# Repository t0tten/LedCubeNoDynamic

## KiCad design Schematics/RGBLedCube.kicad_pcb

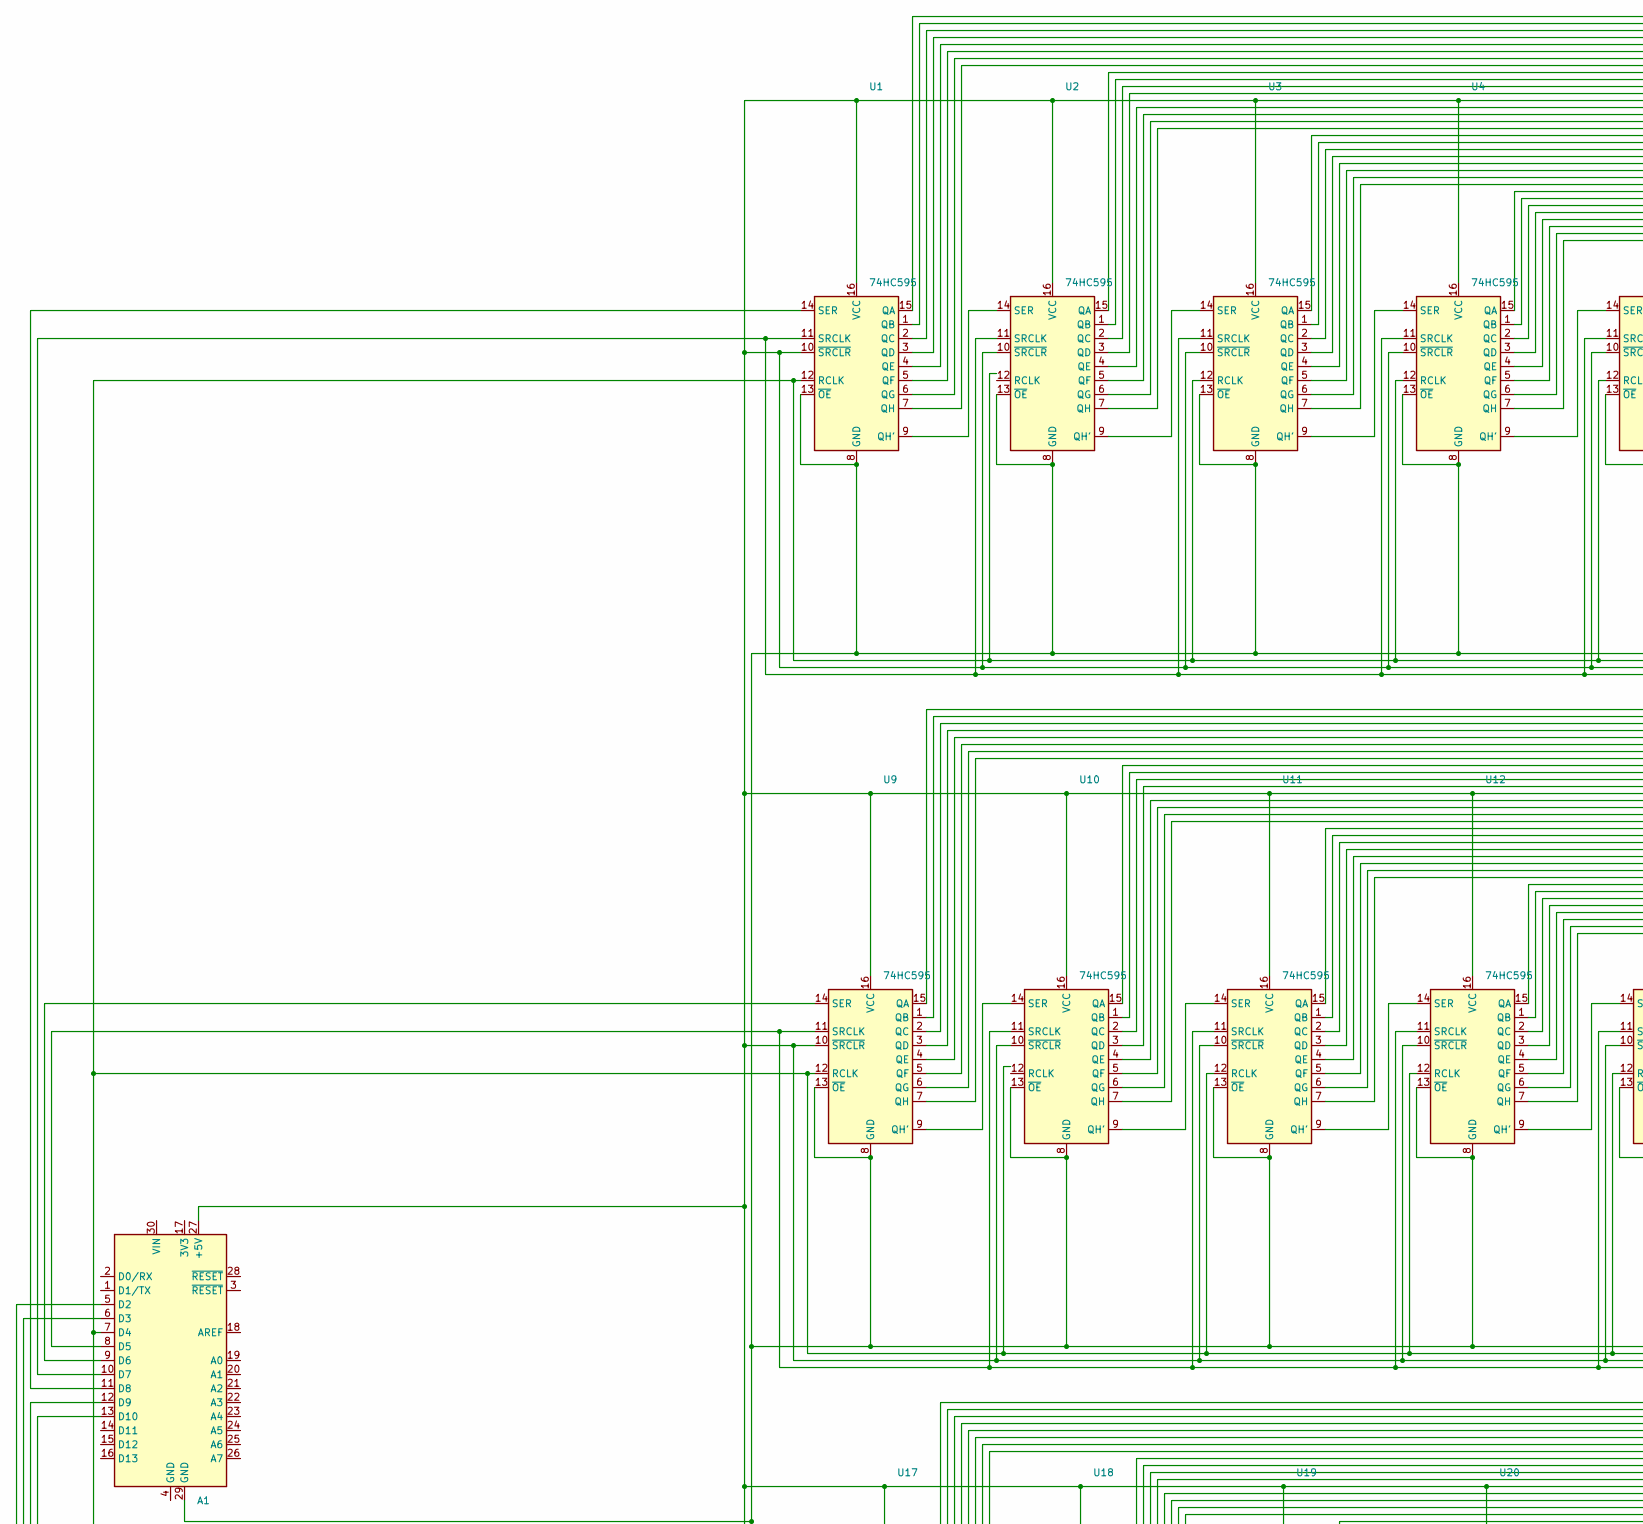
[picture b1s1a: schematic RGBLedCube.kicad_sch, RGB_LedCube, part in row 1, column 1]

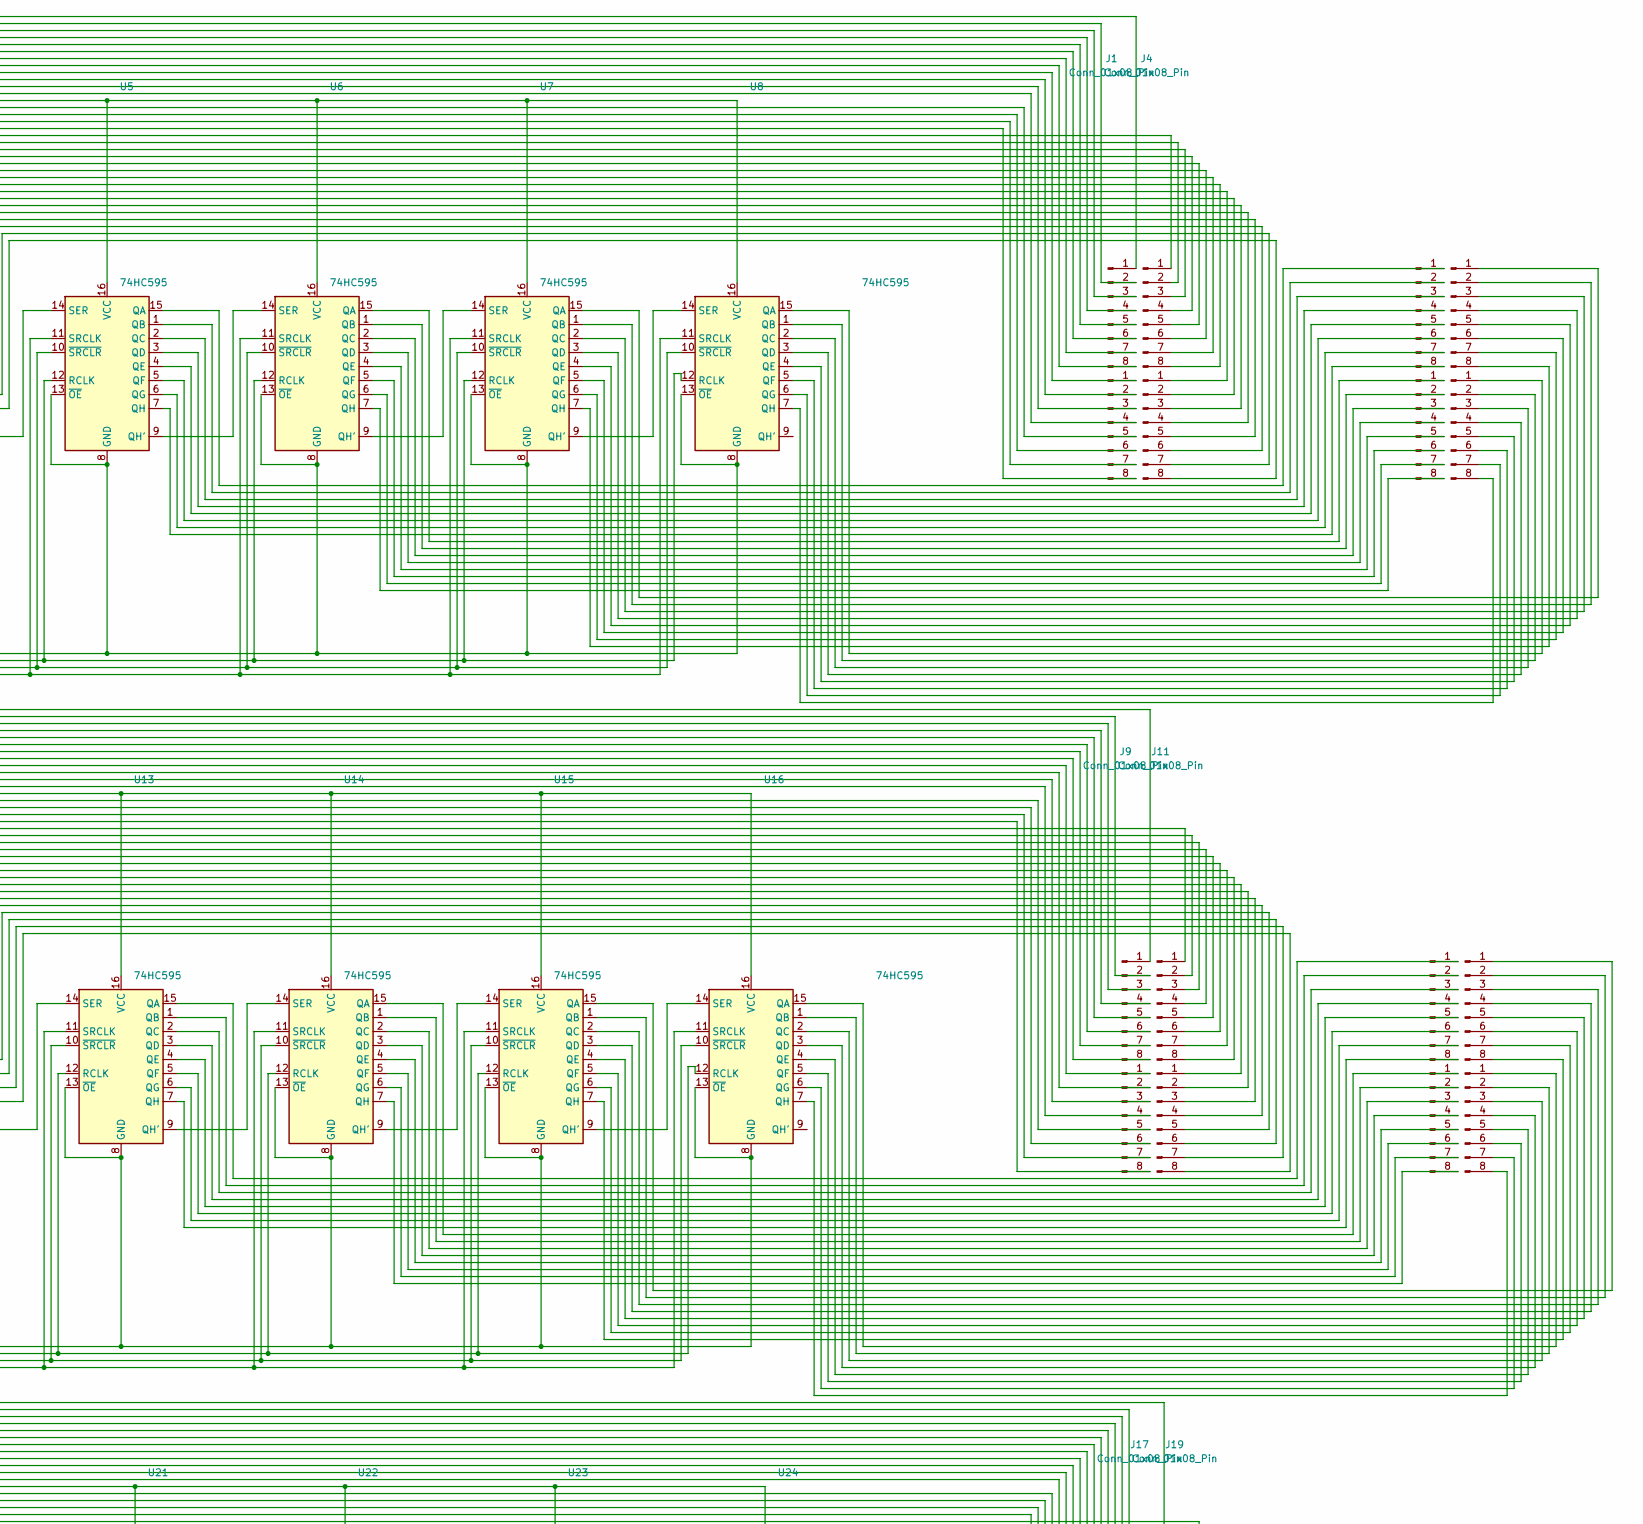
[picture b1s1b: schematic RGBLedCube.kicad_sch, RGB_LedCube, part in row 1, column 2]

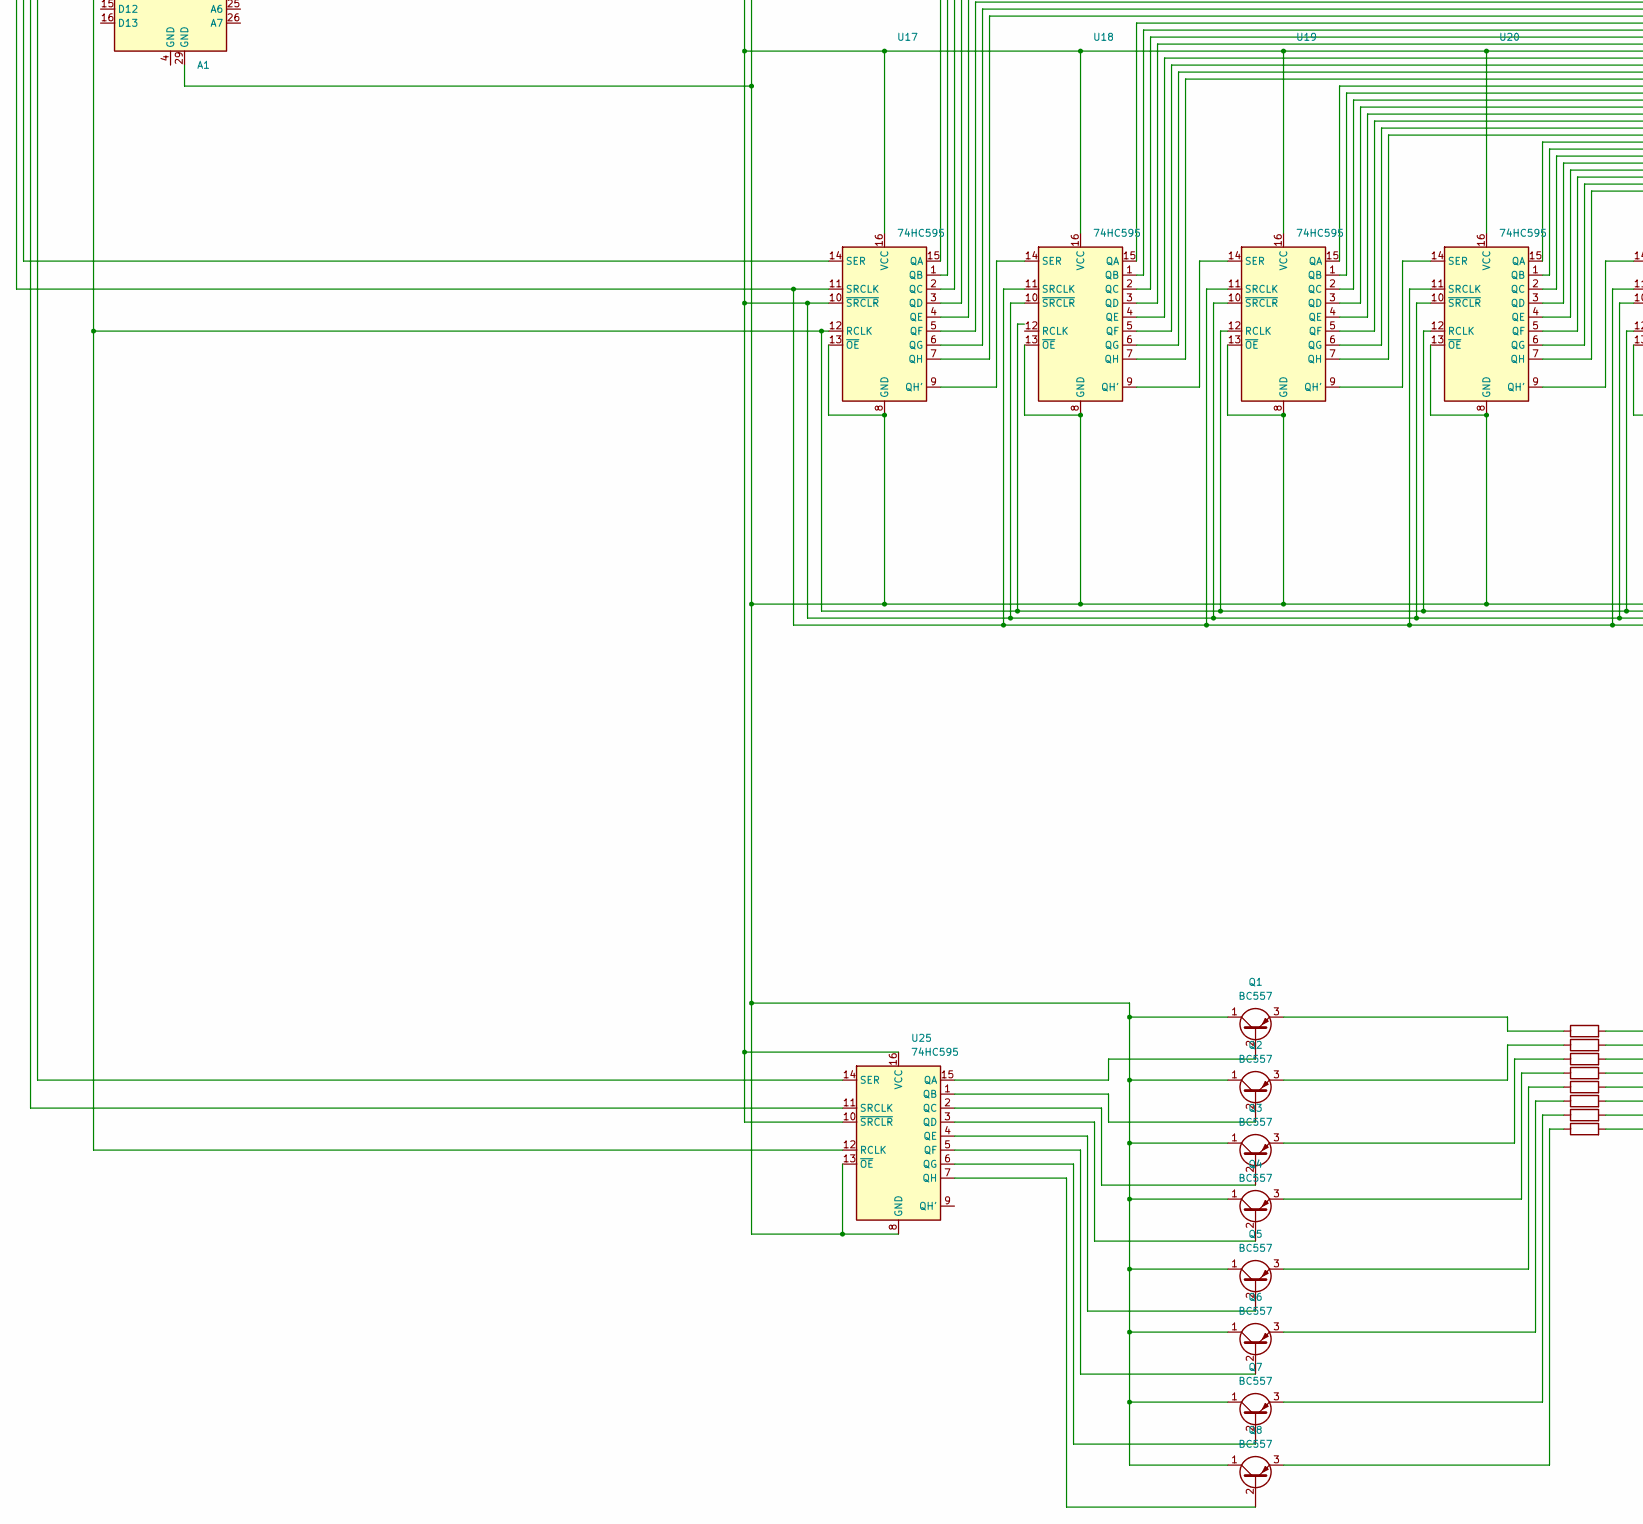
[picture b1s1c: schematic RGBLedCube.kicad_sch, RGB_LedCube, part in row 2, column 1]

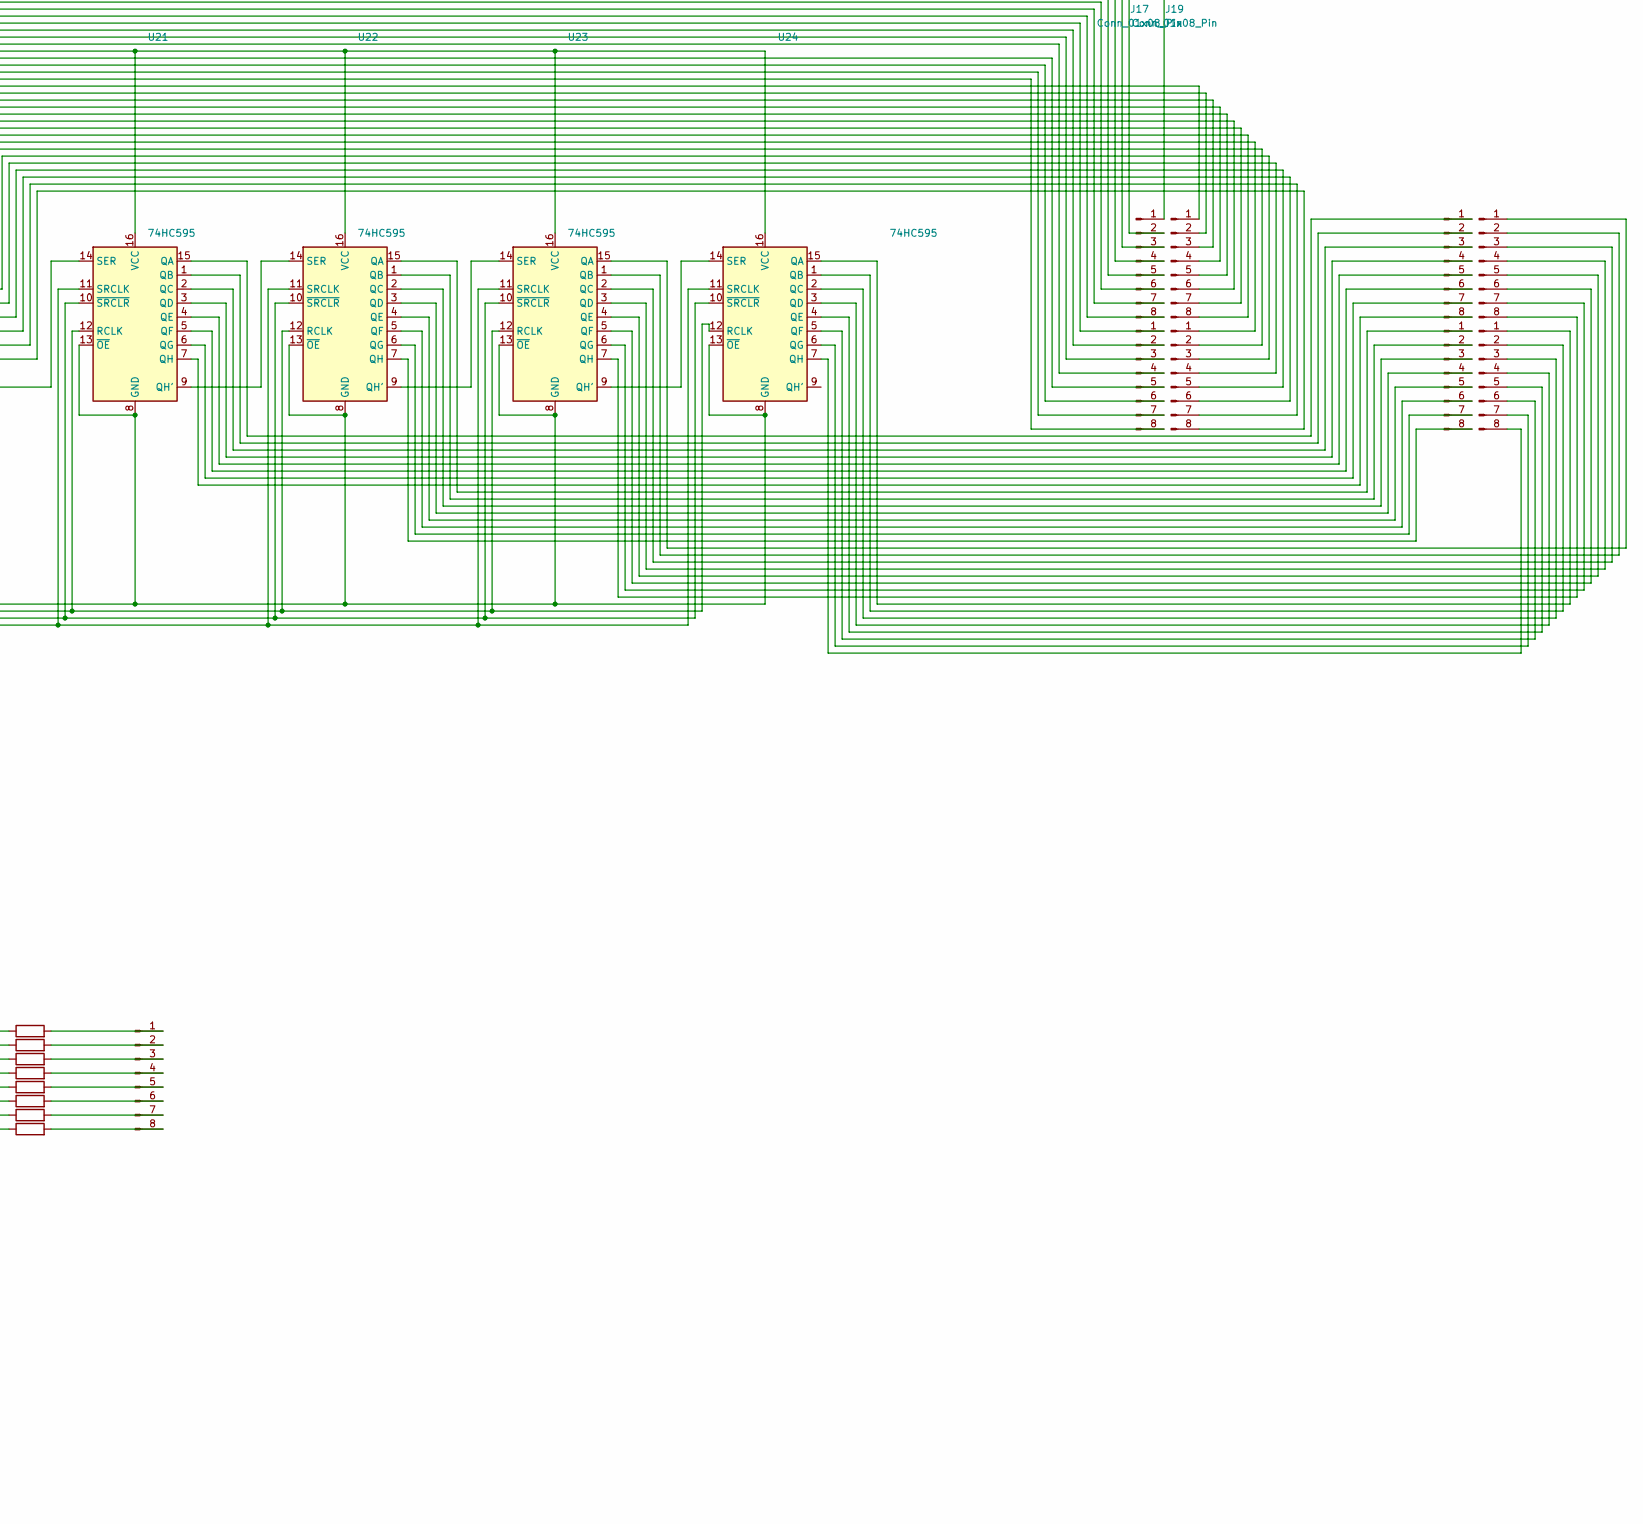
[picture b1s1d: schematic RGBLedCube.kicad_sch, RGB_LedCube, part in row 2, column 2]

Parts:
A1: Arduino_Nano_v2.x; Arduino_Nano
J1, J2, J3, J4, J5, J6, J7, J8, J9, J10, J11, J12, J13, J14, J15, J16, J17, J18, J19, J20, J21, J22, J23, J24, J25: Conn_01x08_Pin; PinHeader_1x08_P2.54mm_Vertical
Q1, Q2, Q3, Q4, Q5, Q6, Q7, Q8: BC557; TO-92_Inline
R1, R2, R3, R4, R5, R6, R7, R8: R; R_Axial_DIN0414_L11.9mm_D4.5mm_P15.24mm_Horizontal
U1, U2, U3, U4, U5, U6, U7, U8, U9, U10, U11, U12, U13, U14, U15, U16, U17, U18, U19, U20, U21, U22, U23, U24, U25: 74HC595; DIP-16_W7.62mm

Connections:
unnamed: A1.27 (+5V), U1.10 (~SRCLR), U1.16 (VCC), U2.10 (~SRCLR), U2.16 (VCC), U3.10 (~SRCLR), U3.16 (VCC), U4.10 (~SRCLR), U4.16 (VCC), U5.10 (~SRCLR), U5.16 (VCC), U6.10 (~SRCLR), U6.16 (VCC), U7.10 (~SRCLR), U7.16 (VCC), U8.10 (~SRCLR), U8.16 (VCC), U9.10 (~SRCLR), U9.16 (VCC), U10.10 (~SRCLR), U10.16 (VCC), U11.10 (~SRCLR), U11.16 (VCC), U12.10 (~SRCLR), U12.16 (VCC), U13.10 (~SRCLR), U13.16 (VCC), U14.10 (~SRCLR), U14.16 (VCC), U15.10 (~SRCLR), U15.16 (VCC), U16.10 (~SRCLR), U16.16 (VCC), U17.10 (~SRCLR), U17.16 (VCC), U18.10 (~SRCLR), U18.16 (VCC), U19.10 (~SRCLR), U19.16 (VCC), U20.10 (~SRCLR), U20.16 (VCC), U21.10 (~SRCLR), U21.16 (VCC), U22.10 (~SRCLR), U22.16 (VCC), U23.10 (~SRCLR), U23.16 (VCC), U24.10 (~SRCLR), U24.16 (VCC), U25.10 (~SRCLR), U25.16 (VCC)
unnamed: A1.5 (D2), U17.11 (SRCLK), U18.11 (SRCLK), U19.11 (SRCLK), U20.11 (SRCLK), U21.11 (SRCLK), U22.11 (SRCLK), U23.11 (SRCLK), U24.11 (SRCLK)
unnamed: A1.6 (D3), U17.14 (SER)
unnamed: A1.7 (D4), U1.12 (RCLK), U3.12 (RCLK), U4.12 (RCLK), U5.12 (RCLK), U6.12 (RCLK), U7.12 (RCLK), U8.12 (RCLK), U9.12 (RCLK), U11.12 (RCLK), U12.12 (RCLK), U13.12 (RCLK), U14.12 (RCLK), U15.12 (RCLK), U16.12 (RCLK), U17.12 (RCLK), U19.12 (RCLK), U20.12 (RCLK), U21.12 (RCLK), U22.12 (RCLK), U23.12 (RCLK), U24.12 (RCLK), U25.12 (RCLK)
unnamed: A1.8 (D5), U9.11 (SRCLK), U10.11 (SRCLK), U11.11 (SRCLK), U12.11 (SRCLK), U13.11 (SRCLK), U14.11 (SRCLK), U15.11 (SRCLK), U16.11 (SRCLK)
unnamed: A1.9 (D6), U9.14 (SER)
unnamed: A1.10 (D7), U1.11 (SRCLK), U2.11 (SRCLK), U3.11 (SRCLK), U4.11 (SRCLK), U5.11 (SRCLK), U6.11 (SRCLK), U7.11 (SRCLK), U8.11 (SRCLK)
unnamed: A1.11 (D8), U1.14 (SER)
unnamed: A1.12 (D9), U25.11 (SRCLK)
unnamed: A1.13 (D10), U25.14 (SER)
unnamed: J1.1, U1.15 (QA)
unnamed: J1.2, U1.1 (QB)
unnamed: J1.3, U1.2 (QC)
unnamed: J1.4, U1.3 (QD)
unnamed: J1.5, U1.4 (QE)
unnamed: J1.6, U1.5 (QF)
unnamed: J1.7, U1.6 (QG)
unnamed: J1.8, U1.7 (QH)
unnamed: J2.1, U4.15 (QA)
unnamed: J2.2, U4.1 (QB)
unnamed: J2.3, U4.2 (QC)
unnamed: J2.4, U4.3 (QD)
unnamed: J2.5, U4.4 (QE)
unnamed: J2.6, U4.5 (QF)
unnamed: J2.7, U4.6 (QG)
unnamed: J2.8, U4.7 (QH)
unnamed: J3.1, U2.15 (QA)
unnamed: J3.2, U2.1 (QB)
unnamed: J3.3, U2.2 (QC)
unnamed: J3.4, U2.3 (QD)
unnamed: J3.5, U2.4 (QE)
unnamed: J3.6, U2.5 (QF)
unnamed: J3.7, U2.6 (QG)
unnamed: J3.8, U2.7 (QH)
unnamed: J4.1, U3.15 (QA)
unnamed: J4.2, U3.1 (QB)
unnamed: J4.3, U3.2 (QC)
unnamed: J4.4, U3.3 (QD)
unnamed: J4.5, U3.4 (QE)
unnamed: J4.6, U3.5 (QF)
unnamed: J4.7, U3.6 (QG)
unnamed: J4.8, U3.7 (QH)
unnamed: J5.1, U5.15 (QA)
unnamed: J5.2, U5.1 (QB)
unnamed: J5.3, U5.2 (QC)
unnamed: J5.4, U5.3 (QD)
unnamed: J5.5, U5.4 (QE)
unnamed: J5.6, U5.5 (QF)
unnamed: J5.7, U5.6 (QG)
unnamed: J5.8, U5.7 (QH)
unnamed: J6.1, U7.15 (QA)
unnamed: J6.2, U7.1 (QB)
unnamed: J6.3, U7.2 (QC)
unnamed: J6.4, U7.3 (QD)
unnamed: J6.5, U7.4 (QE)
unnamed: J6.6, U7.5 (QF)
unnamed: J6.7, U7.6 (QG)
unnamed: J6.8, U7.7 (QH)
unnamed: J7.1, U6.15 (QA)
unnamed: J7.2, U6.1 (QB)
unnamed: J7.3, U6.2 (QC)
unnamed: J7.4, U6.3 (QD)
unnamed: J7.5, U6.4 (QE)
unnamed: J7.6, U6.5 (QF)
unnamed: J7.7, U6.6 (QG)
unnamed: J7.8, U6.7 (QH)
unnamed: J8.1, U8.15 (QA)
unnamed: J8.2, U8.1 (QB)
unnamed: J8.3, U8.2 (QC)
unnamed: J8.4, U8.3 (QD)
unnamed: J8.5, U8.4 (QE)
unnamed: J8.6, U8.5 (QF)
unnamed: J8.7, U8.6 (QG)
unnamed: J8.8, U8.7 (QH)
unnamed: J9.1, U9.15 (QA)
unnamed: J9.2, U9.1 (QB)
unnamed: J9.3, U9.2 (QC)
unnamed: J9.4, U9.3 (QD)
unnamed: J9.5, U9.4 (QE)
unnamed: J9.6, U9.5 (QF)
unnamed: J9.7, U9.6 (QG)
unnamed: J9.8, U9.7 (QH)
unnamed: J10.1, U10.15 (QA)
unnamed: J10.2, U10.1 (QB)
unnamed: J10.3, U10.2 (QC)
unnamed: J10.4, U10.3 (QD)
unnamed: J10.5, U10.4 (QE)
unnamed: J10.6, U10.5 (QF)
unnamed: J10.7, U10.6 (QG)
unnamed: J10.8, U10.7 (QH)
unnamed: J11.1, U11.15 (QA)
unnamed: J11.2, U11.1 (QB)
unnamed: J11.3, U11.2 (QC)
unnamed: J11.4, U11.3 (QD)
unnamed: J11.5, U11.4 (QE)
unnamed: J11.6, U11.5 (QF)
unnamed: J11.7, U11.6 (QG)
unnamed: J11.8, U11.7 (QH)
unnamed: J12.1, U12.15 (QA)
unnamed: J12.2, U12.1 (QB)
unnamed: J12.3, U12.2 (QC)
unnamed: J12.4, U12.3 (QD)
unnamed: J12.5, U12.4 (QE)
unnamed: J12.6, U12.5 (QF)
unnamed: J12.7, U12.6 (QG)
unnamed: J12.8, U12.7 (QH)
unnamed: J13.1, U13.15 (QA)
unnamed: J13.2, U13.1 (QB)
unnamed: J13.3, U13.2 (QC)
unnamed: J13.4, U13.3 (QD)
unnamed: J13.5, U13.4 (QE)
unnamed: J13.6, U13.5 (QF)
unnamed: J13.7, U13.6 (QG)
unnamed: J13.8, U13.7 (QH)
unnamed: J14.1, U14.15 (QA)
unnamed: J14.2, U14.1 (QB)
unnamed: J14.3, U14.2 (QC)
unnamed: J14.4, U14.3 (QD)
unnamed: J14.5, U14.4 (QE)
unnamed: J14.6, U14.5 (QF)
unnamed: J14.7, U14.6 (QG)
unnamed: J14.8, U14.7 (QH)
unnamed: J15.1, U15.15 (QA)
unnamed: J15.2, U15.1 (QB)
unnamed: J15.3, U15.2 (QC)
unnamed: J15.4, U15.3 (QD)
unnamed: J15.5, U15.4 (QE)
unnamed: J15.6, U15.5 (QF)
unnamed: J15.7, U15.6 (QG)
unnamed: J15.8, U15.7 (QH)
unnamed: J16.1, U16.15 (QA)
unnamed: J16.2, U16.1 (QB)
unnamed: J16.3, U16.2 (QC)
unnamed: J16.4, U16.3 (QD)
unnamed: J16.5, U16.4 (QE)
unnamed: J16.6, U16.5 (QF)
unnamed: J16.7, U16.6 (QG)
unnamed: J16.8, U16.7 (QH)
unnamed: J17.1, U17.15 (QA)
unnamed: J17.2, U17.1 (QB)
unnamed: J17.3, U17.2 (QC)
unnamed: J17.4, U17.3 (QD)
unnamed: J17.5, U17.4 (QE)
unnamed: J17.6, U17.5 (QF)
unnamed: J17.7, U17.6 (QG)
unnamed: J17.8, U17.7 (QH)
unnamed: J18.1, U18.15 (QA)
unnamed: J18.2, U18.1 (QB)
unnamed: J18.3, U18.2 (QC)
unnamed: J18.4, U18.3 (QD)
unnamed: J18.5, U18.4 (QE)
unnamed: J18.6, U18.5 (QF)
unnamed: J18.7, U18.6 (QG)
unnamed: J18.8, U18.7 (QH)
unnamed: J19.1, U19.15 (QA)
unnamed: J19.2, U19.1 (QB)
unnamed: J19.3, U19.2 (QC)
unnamed: J19.4, U19.3 (QD)
unnamed: J19.5, U19.4 (QE)
unnamed: J19.6, U19.5 (QF)
unnamed: J19.7, U19.6 (QG)
unnamed: J19.8, U19.7 (QH)
unnamed: J20.1, U20.15 (QA)
unnamed: J20.2, U20.1 (QB)
unnamed: J20.3, U20.2 (QC)
unnamed: J20.4, U20.3 (QD)
unnamed: J20.5, U20.4 (QE)
unnamed: J20.6, U20.5 (QF)
unnamed: J20.7, U20.6 (QG)
unnamed: J20.8, U20.7 (QH)
unnamed: J21.1, U21.15 (QA)
unnamed: J21.2, U21.1 (QB)
unnamed: J21.3, U21.2 (QC)
unnamed: J21.4, U21.3 (QD)
unnamed: J21.5, U21.4 (QE)
unnamed: J21.6, U21.5 (QF)
unnamed: J21.7, U21.6 (QG)
unnamed: J21.8, U21.7 (QH)
unnamed: J22.1, U22.15 (QA)
unnamed: J22.2, U22.1 (QB)
unnamed: J22.3, U22.2 (QC)
unnamed: J22.4, U22.3 (QD)
unnamed: J22.5, U22.4 (QE)
unnamed: J22.6, U22.5 (QF)
unnamed: J22.7, U22.6 (QG)
unnamed: J22.8, U22.7 (QH)
unnamed: J23.1, U23.15 (QA)
unnamed: J23.2, U23.1 (QB)
unnamed: J23.3, U23.2 (QC)
unnamed: J23.4, U23.3 (QD)
unnamed: J23.5, U23.4 (QE)
unnamed: J23.6, U23.5 (QF)
unnamed: J23.7, U23.6 (QG)
unnamed: J23.8, U23.7 (QH)
unnamed: J24.1, U24.15 (QA)
unnamed: J24.2, U24.1 (QB)
unnamed: J24.3, U24.2 (QC)
unnamed: J24.4, U24.3 (QD)
unnamed: J24.5, U24.4 (QE)
unnamed: J24.6, U24.5 (QF)
unnamed: J24.7, U24.6 (QG)
unnamed: J24.8, U24.7 (QH)
unnamed: J25.1, R1.2
unnamed: J25.2, R2.2
unnamed: J25.3, R3.2
unnamed: J25.4, R4.2
unnamed: J25.5, R5.2
unnamed: J25.6, R6.2
unnamed: J25.7, R7.2
unnamed: J25.8, R8.2
unnamed: Q1.2 (B), U25.15 (QA)
unnamed: A1.29 (GND), Q1.1 (C), Q2.1 (C), Q3.1 (C), Q4.1 (C), Q5.1 (C), Q6.1 (C), Q7.1 (C), Q8.1 (C), U1.8 (GND), U1.13 (~OE), U2.8 (GND), U2.13 (~OE), U3.8 (GND), U3.13 (~OE), U4.8 (GND), U4.13 (~OE), U5.8 (GND), U5.13 (~OE), U6.8 (GND), U6.13 (~OE), U7.8 (GND), U7.13 (~OE), U8.8 (GND), U8.13 (~OE), U9.8 (GND), U9.13 (~OE), U10.8 (GND), U10.13 (~OE), U11.8 (GND), U11.13 (~OE), U12.8 (GND), U12.13 (~OE), U13.8 (GND), U13.13 (~OE), U14.8 (GND), U14.13 (~OE), U15.8 (GND), U15.13 (~OE), U16.8 (GND), U16.13 (~OE), U17.8 (GND), U17.13 (~OE), U18.8 (GND), U18.13 (~OE), U19.8 (GND), U19.13 (~OE), U20.8 (GND), U20.13 (~OE), U21.8 (GND), U21.13 (~OE), U22.8 (GND), U22.13 (~OE), U23.8 (GND), U23.13 (~OE), U24.8 (GND), U24.13 (~OE), U25.8 (GND), U25.13 (~OE)
unnamed: Q1.3 (E), R1.1
unnamed: Q2.2 (B), U25.1 (QB)
unnamed: Q2.3 (E), R2.1
unnamed: Q3.2 (B), U25.2 (QC)
unnamed: Q3.3 (E), R3.1
unnamed: Q4.2 (B), U25.3 (QD)
unnamed: Q4.3 (E), R4.1
unnamed: Q5.2 (B), U25.4 (QE)
unnamed: Q5.3 (E), R5.1
unnamed: Q6.2 (B), U25.5 (QF)
unnamed: Q6.3 (E), R6.1
unnamed: Q7.2 (B), U25.6 (QG)
unnamed: Q7.3 (E), R7.1
unnamed: Q8.2 (B), U25.7 (QH)
unnamed: Q8.3 (E), R8.1
unnamed: U1.9 (QH'), U2.14 (SER)
unnamed: U2.9 (QH'), U3.14 (SER)
unnamed: U3.9 (QH'), U4.14 (SER)
unnamed: U4.9 (QH'), U5.14 (SER)
unnamed: U5.9 (QH'), U6.14 (SER)
unnamed: U6.9 (QH'), U7.14 (SER)
unnamed: U7.9 (QH'), U8.14 (SER)
unnamed: U10.9 (QH'), U11.14 (SER)
unnamed: U9.9 (QH'), U10.14 (SER)
unnamed: U11.9 (QH'), U12.14 (SER)
unnamed: U12.9 (QH'), U13.14 (SER)
unnamed: U13.9 (QH'), U14.14 (SER)
unnamed: U14.9 (QH'), U15.14 (SER)
unnamed: U15.9 (QH'), U16.14 (SER)
unnamed: U17.9 (QH'), U18.14 (SER)
unnamed: U18.9 (QH'), U19.14 (SER)
unnamed: U19.9 (QH'), U20.14 (SER)
unnamed: U20.9 (QH'), U21.14 (SER)
unnamed: U21.9 (QH'), U22.14 (SER)
unnamed: U22.9 (QH'), U23.14 (SER)
unnamed: U23.9 (QH'), U24.14 (SER)

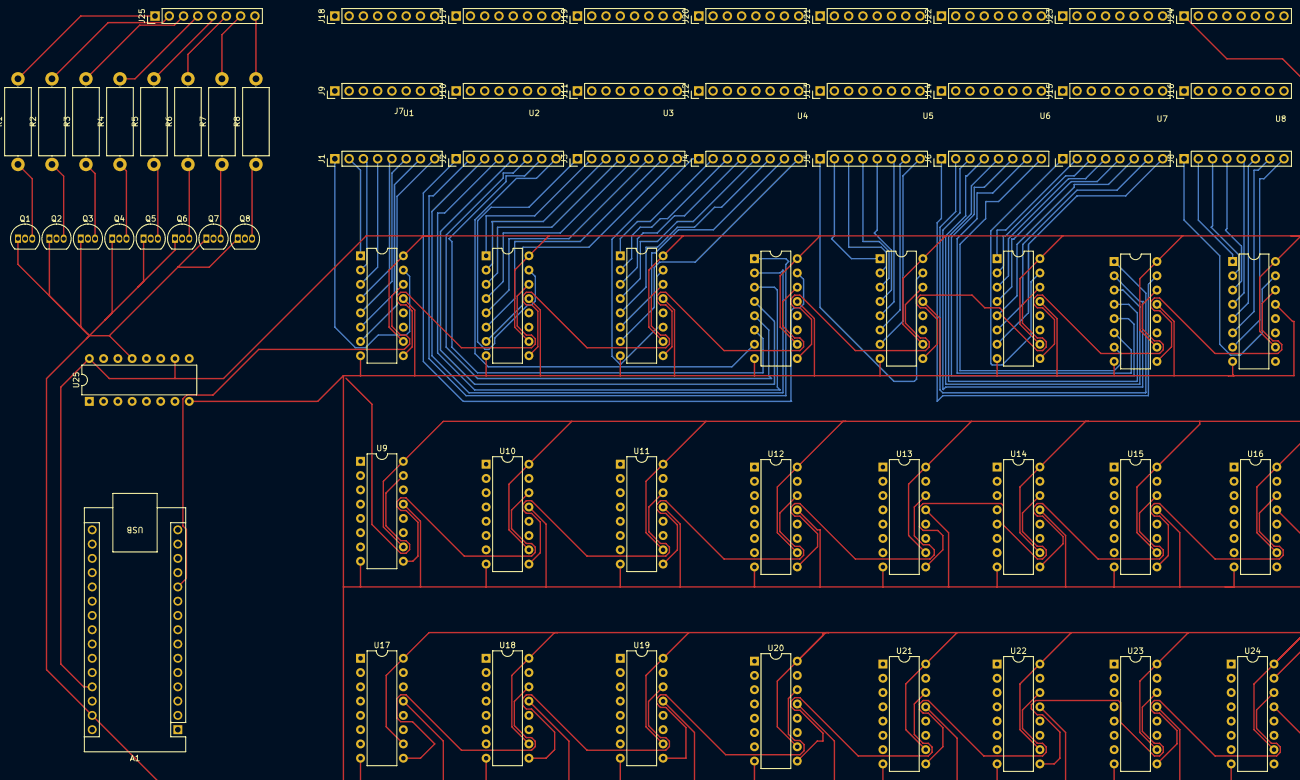
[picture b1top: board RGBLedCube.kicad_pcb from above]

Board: 2 copper layers, 67 parts (0 on the bottom side), 248 nets.

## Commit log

2024-01-11 Add project
    Tracking-Id: EIP
2024-01-12 Fix maze bug
    Also make maze work no matter size of cube.
    Reafctor Animation class a bit.
    Tracking-Id: EIP
2024-01-14 Add schematics folder
    Tracking-Id: EIP
2024-01-15 Add schematics
    Tracking-Id: EIP
2024-01-15 Add PDF schematics
    Tracking-Id: EIP
2024-01-16 Fix lights array bug
    Tracking-Id: EIP
2024-01-16 Add led layout
    20x20
    30x30
    Tracking-Id: EIP
2024-01-16 Add 30x30 small layout
    Tracking-Id: EIP
2024-01-20 Add simulation of file support
    Tracking-Id: EIP
